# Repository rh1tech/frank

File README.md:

# FRANK

FRANK is a hardware emulation platform built around the Raspberry Pi RP2350 (Pico 2 modules and RP2350A QFN). RP2040 / Pico still works in FRANK's socket, but in practice only a handful of firmware (mainly the older ZX Spectrum cores) still targets RP2040. Everything modern (IBM PC, NES, SNES, Genesis, the DOOM / id Tech 1 ports, FRANK OS, and so on) is RP2350-only.

It started as a fork of the [Murmulator](https://murmulator.tilda.ws/) project by [Alex Ekb](https://t.me/Alex_Eburg). Over time it picked up extra video outputs, audio paths, USB and WiFi support, and several form factors.

The name comes from "Frankenstein". The board is stitched together from parts of different projects, so the name stuck.

## Looking for an older board?

This repository now ships only the boards under `hardware/` that are actively maintained. The `accessories/` and `archive/` directories are gone. Older revisions, retired boards, and accessory adapters such as HDMI2VGA and USB2PS2 live in [rh1tech/frank-archive](https://github.com/rh1tech/frank-archive).

Experimental and work-in-progress designs live in [rh1tech/frank-lab](https://github.com/rh1tech/frank-lab).

## The boards in this repo

Ten maintained boards and one published prototype, each with its own KiCad project, gerbers, BOM and assembly drawings, plus two add-on modules ([TurboSound](#modules) and [Hecate](#modules)) and three [retro-CPU boards](#retro-cpu-boards).

| Board | Render | PCB size | Compute | Best for |
|-------|:------:|----------|---------|----------|
| [FRANK Next](./hardware/frank_next) |  | 99.0 × 53.98 mm | RP2350B + RP2350A, both on-board | **Flagship.** Two RP2350 dies, on-board ESP8266EX WiFi, CH343P console, three USB-A host ports. |
| [MegaFRANK](./hardware/megafrank) |  | 149.9 × 99.5 mm | Pimoroni PGA2350 (RP2350B module) | Maximal board — every output plus on-board dual-AY TurboSound, DS3231 RTC and dual power input. |
| [FRANK PGA](./hardware/frank_pga) |  | 99.5 × 83.1 mm | Pimoroni PGA2350 (RP2350A module) | Every output on one PCB, native USB host with multiplexer, ESD-protected. |
| [FRANK](./hardware/frank) |  | 99.5 × 83.1 mm | Raspberry Pi Pico / Pico 2 (socket) + RP2040-Zero | Socketed alternative. Easiest to solder, swap Pico modules at will, USB-to-PS/2 helper on board. |
| [Old Skool FRANK](./hardware/oldskool) |  | 100.0 × 79.0 mm | Pimoroni PGA2350 (RP2350B module) | The retro-connector board: HDMI **and** VGA, hardware PS/2, DB9 gamepad. Only 2-layer design, easiest to hand-assemble. |
| [MiniFRANK](./hardware/minifrank) |  | 85.6 × 53.98 mm | RP2350A QFN, on-board | Compact full-feature board with WiFi, VGA, HDMI and one gamepad port. |
| [FRANK Core 2U](./hardware/frank_core2u) |  | 67.0 × 55.0 mm | RP2350B + RP2350A, both on-board | Smallest usable dual-die board. Video, sound, storage and USB only — no WiFi, no RTC. |
| [FRANK Core 2 Proto](./hardware/frank_core2_proto) |  | 55.0 × 55.0 mm | RP2350B + RP2350A, both on-board | Prototype. Core 2U without the USB host side — the dual-die topology at its smallest. |
| [MicroFRANK](./hardware/microfrank) |  | 32 × 74 mm | RP2350A QFN, on-board | Smallest single-die board. HDMI only, no hardware PS/2 or DB9 gamepad. Keyboards, mice and gamepads connect over the stacked USB host. |
| [ZeroFRANK](./hardware/zerofrank) |  | 65 × 25 mm | RP2350A QFN, on-board | Smallest RP2350A board. HDMI only, USB host for input, on-board flash + PSRAM + I²S audio. |
| [Nyx](./hardware/nyx) |  | 51 × 21 mm | RP2350B QFN, on-board | Open-source Pico 2 clone with built-in PSRAM. Drop-in replacement for Pico Plus 2 in the FRANK socket. |

The full-size and compact boards use the M2 GPIO layout, so any firmware build for M2 runs on them (subject to the feature differences below). FRANK Next, Core 2U and Core 2 Proto are the exception: they carry two RP2350 dies and firmware must be built for that split, or the slave simply sits idle. Nyx is a compute module — it plugs into the FRANK socket and provides the RP2350B, flash and PSRAM; the FRANK motherboard provides all the I/O.

### Comparison: full-size boards

| Feature | MegaFRANK | FRANK PGA | FRANK | Old Skool |
|---------|:---------:|:---------:|:-----:|:---------:|
| Compute | Pimoroni PGA2350 | Pimoroni PGA2350 | Pico / Pico 2 (socket) | Pimoroni PGA2350 |
| Copper layers | 4 | 4 | 4 | **2** |
| On-board flash | via module | via module | via module | via module |
| On-board PSRAM | via module | via module | via module | via module |
| HDMI output | Yes | Yes | Yes | Yes |
| VGA output | Yes | Yes | Yes | Yes |
| Composite (RCA) | Yes | Yes | Yes | — |
| TFT display header | Yes | Yes | Yes | — |
| Hardware PS/2 port | Yes | Yes | Yes | Yes |
| USB-emulated PS/2 (RP2040-Zero) | — | — | Yes | — |
| Gamepad ports (DB9) | 2 | 2 | 2 | 1 |
| Stacked USB Type-A host | Yes | Yes | Yes | Yes |
| USB hub | MW7211A | MW7211A | MW7211A | MW7211A |
| USB host multiplexer | 74HC4052D | 74HC4052D | — | 74HC4052 |
| USBLC6 ESD protection | Yes | Yes | — | — |
| WiFi | ESP-01S socket | ESP-01S socket | ESP-01S socket | ESP-01S socket |
| Real-time clock | DS3231 | — | — | — |
| Tape input (3.5mm) | Yes | Yes | Yes | Yes |
| Audio DAC | TDA1387 | TDA1387 | TDA1387 | TDA1545A + LM358 |
| PAM8403 speaker amp | Yes | Yes | Yes | — |
| Power input | DC barrel jack (×2) | DC barrel jack | DC barrel jack | USB-C / USB-B |
| Voltage regulator | MP1584 buck + AMS1117 LDO | MP1584 buck + AMS1117 LDO | MP1584 buck + AMS1117 LDO | AMS1117 LDO |
| Mounting holes | 4 × 2.7 mm | 4 × 2.7 mm | 4 × 2.7 mm | 4 × 2.7 mm |

On-board TurboSound (dual YM2149), a DS3231 real-time clock and a DS2401 silicon serial number are unique to MegaFRANK. Old Skool FRANK is the only 2-layer board in the repo, which makes it the friendliest to hand-assembly and rework.

### Comparison: compact boards

| Feature | FRANK Next | MiniFRANK | Core 2U | Core 2 Proto | MicroFRANK | ZeroFRANK |
|---------|:----------:|:---------:|:-------:|:------------:|:----------:|:---------:|
| Compute | RP2350B + RP2350A | RP2350A QFN | RP2350B + RP2350A | RP2350B + RP2350A | RP2350A QFN | RP2350A QFN |
| On-board flash | 2 × W25Q128 | W25Q128 | 2 × W25Q128 | 2 × W25Q128 | W25Q128 | W25Q128 |
| On-board PSRAM | 2 × 8 MB | 8 MB | 2 × 8 MB | 2 × 8 MB | 8 MB | 8 MB |
| HDMI output | Yes | Yes | Yes | Yes | Yes | Yes |
| VGA output | — | Yes | — | — | — | — |
| Hardware PS/2 port | — | Yes | — | — | — | — |
| Gamepad ports (DB9) | — | 1 | — | — | — | — |
| USB Type-A host ports | 3 | 2 (stacked) | 2 | — | 2 (stacked) | — (USB-C PIO host) |
| USB hub | CH334F | MW7211A | MW7211A | — | MW7211A | — |
| USB host multiplexer | TS3USB221 × 2 | TS3USB221 | TS3USB221 | — | TS3USB221 | — |
| USB serial bridge | CH343P | — | — | — | — | — |
| WiFi | ESP8266EX on-board | ESP-01S socket | — | — | — | — |
| Real-time clock | DS3231MZ | — | — | — | — | — |
| Tape input (3.5mm) | Yes | Yes | Yes | — | — | — |
| Audio DAC | TLV320DAC3100 | TDA1387 | TDA1387T + LM358 | TDA1387T + LM358 | TDA1387 | TDA1387 |
| Power input | USB-C | USB-C | USB-C | USB-C × 2 | USB-C | USB-C |
| Voltage regulator | SY8089 buck | AMS1117 LDO | AMS1117 LDO | AMS1117 LDO | ME6211 LDO | AMS1117 LDO |
| Mounting holes | 4 × 2.5 mm plated | 4 × 2.7 mm | 4 × 2.5 mm plated | 4 × 2.5 mm plated | 4 × 2.7 mm | 4 × 2.7 mm |

FRANK Next, Core 2U and Core 2 Proto share the dual-RP2350 architecture: an RP2350B master for emulation and an RP2350A slave for USB host, audio and housekeeping. Core 2U and Core 2 Proto come from a different subsystem generation than FRANK Next — ESP-PSRAM64H memory, a discrete TDA1387T audio chain instead of the TLV320DAC3100 codec, an AMS1117 LDO instead of a switching buck, and no WiFi or RTC. Core 2 Proto is Core 2U minus its host side: same two dies, no hub, no USB-A, no tape input and no power switch.

## Retro CPU boards

These are not emulation boards. Each carries a real vintage CPU in a DIP-40 socket, with an RP2350B acting as the chipset — memory, video, storage and I/O. They do not run the FRANK emulation firmware; each has its own chipset firmware.

| Board | Render | PCB size | CPU | Notes |
|-------|:------:|----------|-----|-------|
| [XT8086 Alpha](./hardware/xt8086_alpha) |  | 99.9 × 78.0 mm | Intel 8086 (minimum mode) | The earlier 8086 design: PGA2350 module, VGA and composite outputs. Superseded by XT8086 Beta, now in [frank-lab](https://github.com/rh1tech/frank-lab). |

### Modules

Two add-on modules ship alongside the boards:

| Module | Render | PCB size | What it is |
|--------|:------:|----------|------------|
| [TurboSound](./hardware/turbosound) |  | 42 × 79.5 mm | Dual YM2149 / AY-3-8910 sound expansion (socketed DIP-40). **Currently supported only by [MiniFRANK](./docs/minifrank.md)** via its expansion header. |
| [Hecate](./hardware/hecate) |  | 53 × 29 mm | Standalone RP2040 USB-to-PS/2 bridge board. Runs the [Hecate firmware](https://github.com/rh1tech/hecate); presents USB keyboards and mice as PS/2 devices. |

## Supported software

Over thirty emulators and native ports run on FRANK boards.

### Console emulators

| Firmware | Platform | Repository | PSRAM required |
|----------|----------|------------|----------------|
| frank-nes | NES / Famicom (Dendy) | [frank-nes](https://github.com/rh1tech/frank-nes) | Yes (8 MB) |
| frank-snes | SNES / Super Famicom | [frank-snes](https://github.com/rh1tech/frank-snes) | Yes (8 MB) |
| frank-genesis | Sega Genesis / Mega Drive | [frank-genesis](https://github.com/rh1tech/frank-genesis) | Yes (8 MB) |
| frank-c64 | Commodore 64 | [frank-c64](https://github.com/rh1tech/frank-c64) | Yes (8 MB) |
| frank-apple | Apple IIe | [frank-apple](https://github.com/rh1tech/frank-apple) | Optional |
| frank-msx | MSX / MSX2 / MSX2+ (fMSX core) | [frank-msx](https://github.com/rh1tech/frank-msx) | Yes (8 MB) |

### PC emulation

| Firmware | Platform | Repository | PSRAM required |
|----------|----------|------------|----------------|
| frank-386 | IBM PC i386 (DOS, Windows 3.x/95, Linux) | [frank-386](https://github.com/rh1tech/frank-386) | Yes (8 MB) |

### Game engine ports

| Firmware | Game | Repository | PSRAM required |
|----------|------|------------|----------------|
| frank-idtech1 | DOOM, Heretic, Hexen, Strife (all-in-one) | [frank-idtech1](https://github.com/rh1tech/frank-idtech1) | Yes (8 MB) |
| frank-doom | DOOM (standalone) | [frank-doom](https://github.com/rh1tech/frank-doom) | Yes (8 MB) |
| frank-heretic | Heretic | [frank-heretic](https://github.com/rh1tech/frank-heretic) | Yes (8 MB) |
| frank-wolf3d | Wolfenstein 3D | [frank-wolf3d](https://github.com/rh1tech/frank-wolf3d) | Yes (8 MB) |
| frank-duke3d | Duke Nukem 3D | [frank-duke3d](https://github.com/rh1tech/frank-duke3d) | Yes (8 MB) |
| frank-prince | Prince of Persia | [frank-prince](https://github.com/rh1tech/frank-prince) | Yes (8 MB) |
| frank-digger | Digger Remastered | [frank-digger](https://github.com/rh1tech/frank-digger) | No |
| frank-quest | ScummVM (AGI, SCI, SCUMM v1–v7, GOB, KYRA — King's Quest, Monkey Island, Day of the Tentacle, Full Throttle, Gobliiins, Kyrandia and more) | [frank-quest](https://github.com/rh1tech/frank-quest) | Yes (8 MB) |

### OS and utilities

| Firmware | Description | Repository | PSRAM required |
|----------|-------------|------------|----------------|
| frank-os | Full desktop OS (Windows 95-style GUI, apps, built-in emulators) | [frank-os](https://github.com/rh1tech/frank-os) | Yes (8 MB) |
| frank-kickstart | UF2 firmware launcher with SD card browser | [frank-kickstart](https://github.com/rh1tech/frank-kickstart) | Optional |
| frank-manul | Text-mode web browser (HTTP/HTTPS via ESP-01 WiFi) | [frank-manul](https://github.com/rh1tech/frank-manul) | Yes (8 MB) |
| frank-netcard | AT modem firmware for the ESP-01 WiFi module | [frank-netcard](https://github.com/rh1tech/frank-netcard) | No |

### Murmulator firmware

The original [Murmulator](https://murmulator.ru/) project provides additional firmware that runs on FRANK boards as well:

**ZX Spectrum cores:** ZX Spectrum 48K / 128K / +3e (tecnocat, pico-spec, frut-bat, ZX Speccy P, murmulator), ZX Elf (pico-alf).

**Other cross-platform emulators:** MS-DOS IBM PC XT 8088, BK-0010 / BK-0011M, Radio 86RK, Macintosh, Atari 800, NES / Famicom / Dendy, Sega Master System / Game Gear, NEC PC Engine / TurboGrafx-16, Nintendo GameBoy / GameBoy Color, Watara Supervision, Atari Lynx, Bandai Wonderswan / Wonderswan Color, NeoGeo Pocket Color, Gamate, Game & Watch / Elektronika.

**Tools and applications:** MurmulatorOS, Picomite MMBasic, VersaTerm, the original Murmulator bootloader.

### Other compatible boards

Most firmware also runs on:

- Murmulator (M1 and M2)
- Olimex PICO-PC (some firmware)
- Waveshare RP2350-PiZero (some firmware)

## Getting started

1. Order or fab the PCB (gerbers are in each board's `gerbers/` directory).
2. Source the components using the BOM (`hardware/<board>/docs/<rev>/bom.html`).
3. Solder following the [board-specific guide](./docs/), starting with the smallest passives and working outwards.
4. Flash firmware: hold BOOTSEL on the RP chip, plug USB, release, copy a `.uf2` file to the drive that appears (or use `picotool load`).
5. Insert an SD card with ROMs, WADs or disk images.
6. Plug in a display (HDMI or VGA), keyboard (PS/2 or USB) and gamepad.

For quick switching between firmware, flash [frank-kickstart](https://github.com/rh1tech/frank-kickstart) first. It gives you a graphical launcher that re-flashes from SD without touching BOOTSEL again.

## PSRAM

Most modern firmware (frank-os, frank-quest, frank-386, frank-genesis, frank-snes, frank-msx, frank-idtech1, frank-doom and so on) needs 8 MB of PSRAM. Some firmware refuses to boot without it: frank-quest installs a custom dlmalloc backed entirely by external PSRAM (`drivers/psram_init.c`, `drivers/dlmalloc.c`), because the runtime (heap-allocated game state, decoded resources, mixer ring buffers, font caches) does not fit in the RP2350's 520 KB of SRAM.

How you get PSRAM depends on the board:

- **FRANK Next, Core 2U and Core 2 Proto**: 8 MB PSRAM per die, both dies on-board. Nothing to do.
- **MiniFRANK, MicroFRANK and ZeroFRANK**: PSRAM is already on-board (8 MB). Nothing to do.
- **FRANK PGA, MegaFRANK and Old Skool FRANK**: the Pimoroni PGA2350 module already includes 8 MB PSRAM. Nothing to do.
- **FRANK**: the socketed Pico 2 has no PSRAM by default. Three ways to fix this:
  1. **Pimoroni Pico Plus 2 (recommended).** A ready-made Pico 2 with 8 MB PSRAM. Drop it into the socket and you are done.
  2. **Build a [Nyx](./hardware/nyx)**, an open-source RP2350B board with integrated 16 MB flash and 8 MB PSRAM. Same form factor as Pico 2, drops straight into the socket.
  3. **Solder a PSRAM chip on top of the flash chip of an RP2350 clone.** SOP-8 flash chips are mostly only on clones (typically the black boards), not on a genuine Pico 2.

## Repo layout

```
hardware/      Board KiCad projects (frank_next, megafrank, frank_pga, frank,
               oldskool, minifrank, frank_core2u, frank_core2_proto, microfrank,
               zerofrank, nyx), the retro-CPU board xt8086_alpha, plus the turbosound and hecate modules
docs/          Shared component datasheets and assembly notes
software/      Pre-built UF2s. Currently ships Hecate, the USB-to-PS/2 bridge
               firmware for FRANK's on-board RP2040-Zero. Once flashed, a USB
               keyboard or mouse appears on the hardware PS/2 lines.
               Source: https://github.com/rh1tech/hecate
```

## Documentation

Each board and module has its own assembly and usage guide:

- [FRANK Next assembly and usage guide](./docs/frank_next.md)
- [MegaFRANK assembly and usage guide](./docs/megafrank.md)
- [FRANK PGA assembly and usage guide](./docs/frank_pga.md)
- [FRANK assembly and usage guide](./docs/frank.md)
- [Old Skool FRANK assembly and usage guide](./docs/oldskool.md)
- [MiniFRANK assembly and usage guide](./docs/minifrank.md)
- [FRANK Core 2U assembly and usage guide](./docs/frank_core2u.md)
- [FRANK Core 2 Proto assembly and usage guide](./docs/frank_core2_proto.md)
- [MicroFRANK assembly and usage guide](./docs/microfrank.md)
- [ZeroFRANK assembly and usage guide](./docs/zerofrank.md)
- [Nyx assembly and usage guide](./docs/nyx.md)
- [TurboSound module guide](./docs/turbosound.md)
- [Hecate (USB-to-PS/2 bridge) guide](./docs/hecate.md)

The `hardware/<board>/docs/` directories also contain auto-generated BOMs (`bom.html`) and assembly drawings (`assembly.pdf`, `schematics.pdf`) for each PCB revision.

## Links

- [rh1.tech/projects/frank](https://rh1.tech/projects/frank) — project website
- [rh1tech/frank-archive](https://github.com/rh1tech/frank-archive) — older boards and accessories
- [rh1tech/frank-lab](https://github.com/rh1tech/frank-lab) — experimental designs

### Firmware repositories

Console emulators:

- [frank-nes](https://github.com/rh1tech/frank-nes) — NES / Famicom (Dendy)
- [frank-snes](https://github.com/rh1tech/frank-snes) — SNES / Super Famicom
- [frank-genesis](https://github.com/rh1tech/frank-genesis) — Sega Genesis / Mega Drive
- [frank-c64](https://github.com/rh1tech/frank-c64) — Commodore 64
- [frank-apple](https://github.com/rh1tech/frank-apple) — Apple IIe
- [frank-msx](https://github.com/rh1tech/frank-msx) — MSX / MSX2 / MSX2+

PC emulation:

- [frank-386](https://github.com/rh1tech/frank-386) — IBM PC i386 (DOS, Windows 3.x/95, Linux)

Game engine ports:

- [frank-idtech1](https://github.com/rh1tech/frank-idtech1) — DOOM, Heretic, Hexen, Strife (all-in-one)
- [frank-doom](https://github.com/rh1tech/frank-doom) — DOOM (standalone)
- [frank-heretic](https://github.com/rh1tech/frank-heretic) — Heretic
- [frank-wolf3d](https://github.com/rh1tech/frank-wolf3d) — Wolfenstein 3D
- [frank-duke3d](https://github.com/rh1tech/frank-duke3d) — Duke Nukem 3D
- [frank-prince](https://github.com/rh1tech/frank-prince) — Prince of Persia
- [frank-digger](https://github.com/rh1tech/frank-digger) — Digger Remastered
- [frank-quest](https://github.com/rh1tech/frank-quest) — ScummVM (AGI, SCI, SCUMM, GOB, KYRA)

OS and utilities:

- [frank-os](https://github.com/rh1tech/frank-os) — Full desktop OS with built-in emulators
- [frank-kickstart](https://github.com/rh1tech/frank-kickstart) — UF2 firmware launcher
- [frank-manul](https://github.com/rh1tech/frank-manul) — Text-mode web browser
- [frank-netcard](https://github.com/rh1tech/frank-netcard) — AT modem firmware for ESP-01
- [hecate](https://github.com/rh1tech/hecate) — USB-to-PS/2 bridge for the RP2040-Zero

## Author

Mikhail Matveev — software engineer and hardware developer based in Thessaloniki, Greece. Background in software architecture, QA and open-source development. Builds retro computing hardware and writes firmware for fun. More projects at [rh1.tech](https://rh1.tech).

## License

&copy; 2026 Mikhail Matveev, <xtreme@rh1.tech>

GPL v3. See [LICENSE](./LICENSE).

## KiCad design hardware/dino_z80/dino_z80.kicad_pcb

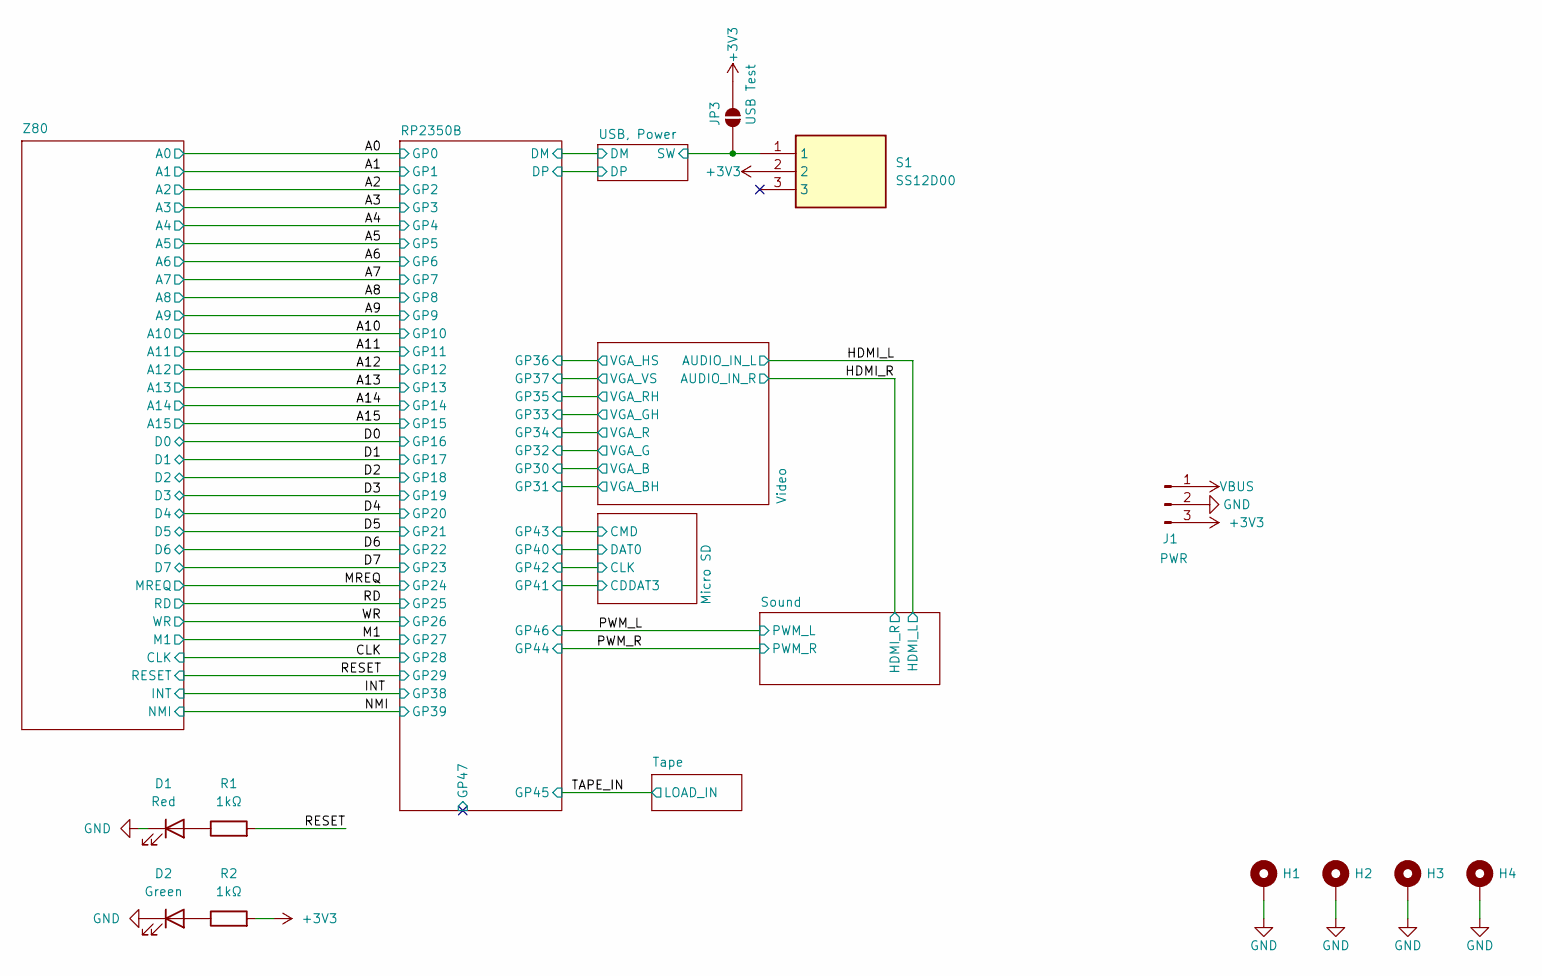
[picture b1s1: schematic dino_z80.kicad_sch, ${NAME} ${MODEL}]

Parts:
D1: Red; LED_0805_2012Metric_Pad1.15x1.40mm_HandSolder
D2: Green; LED_0805_2012Metric_Pad1.15x1.40mm_HandSolder
H1, H2, H3, H4: Hole 2.5mm; MountingHole_2.5mm_Pad_Via
J1: PWR; PinHeader_1x03_P2.54mm_Vertical
JP3: USB Test; SolderJumper-2_P1.3mm_Open_Pad1.0x1.5mm
R1, R2: 1kΩ; R_0603_1608Metric
S1: SS12D00; Switch_Slide_SS12D00; Mouser Part Number 611-SK12D07VG3NS

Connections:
+3V3: J1.3, JP3.1 (A), R2.2, S1.2; also elsewhere on the board
/RESET: R1.2; also elsewhere on the board
/USB, Power/SW: JP3.2 (B), S1.1; also elsewhere on the board
GND: D1.1 (K), D2.1 (K), H1.1 (1_1), H2.1 (1_1), H3.1 (1_1), H4.1 (1_1), J1.2; also elsewhere on the board
unnamed: D1.2 (A), R1.1
unnamed: D2.2 (A), R2.1
VBUS: J1.1; also elsewhere on the board

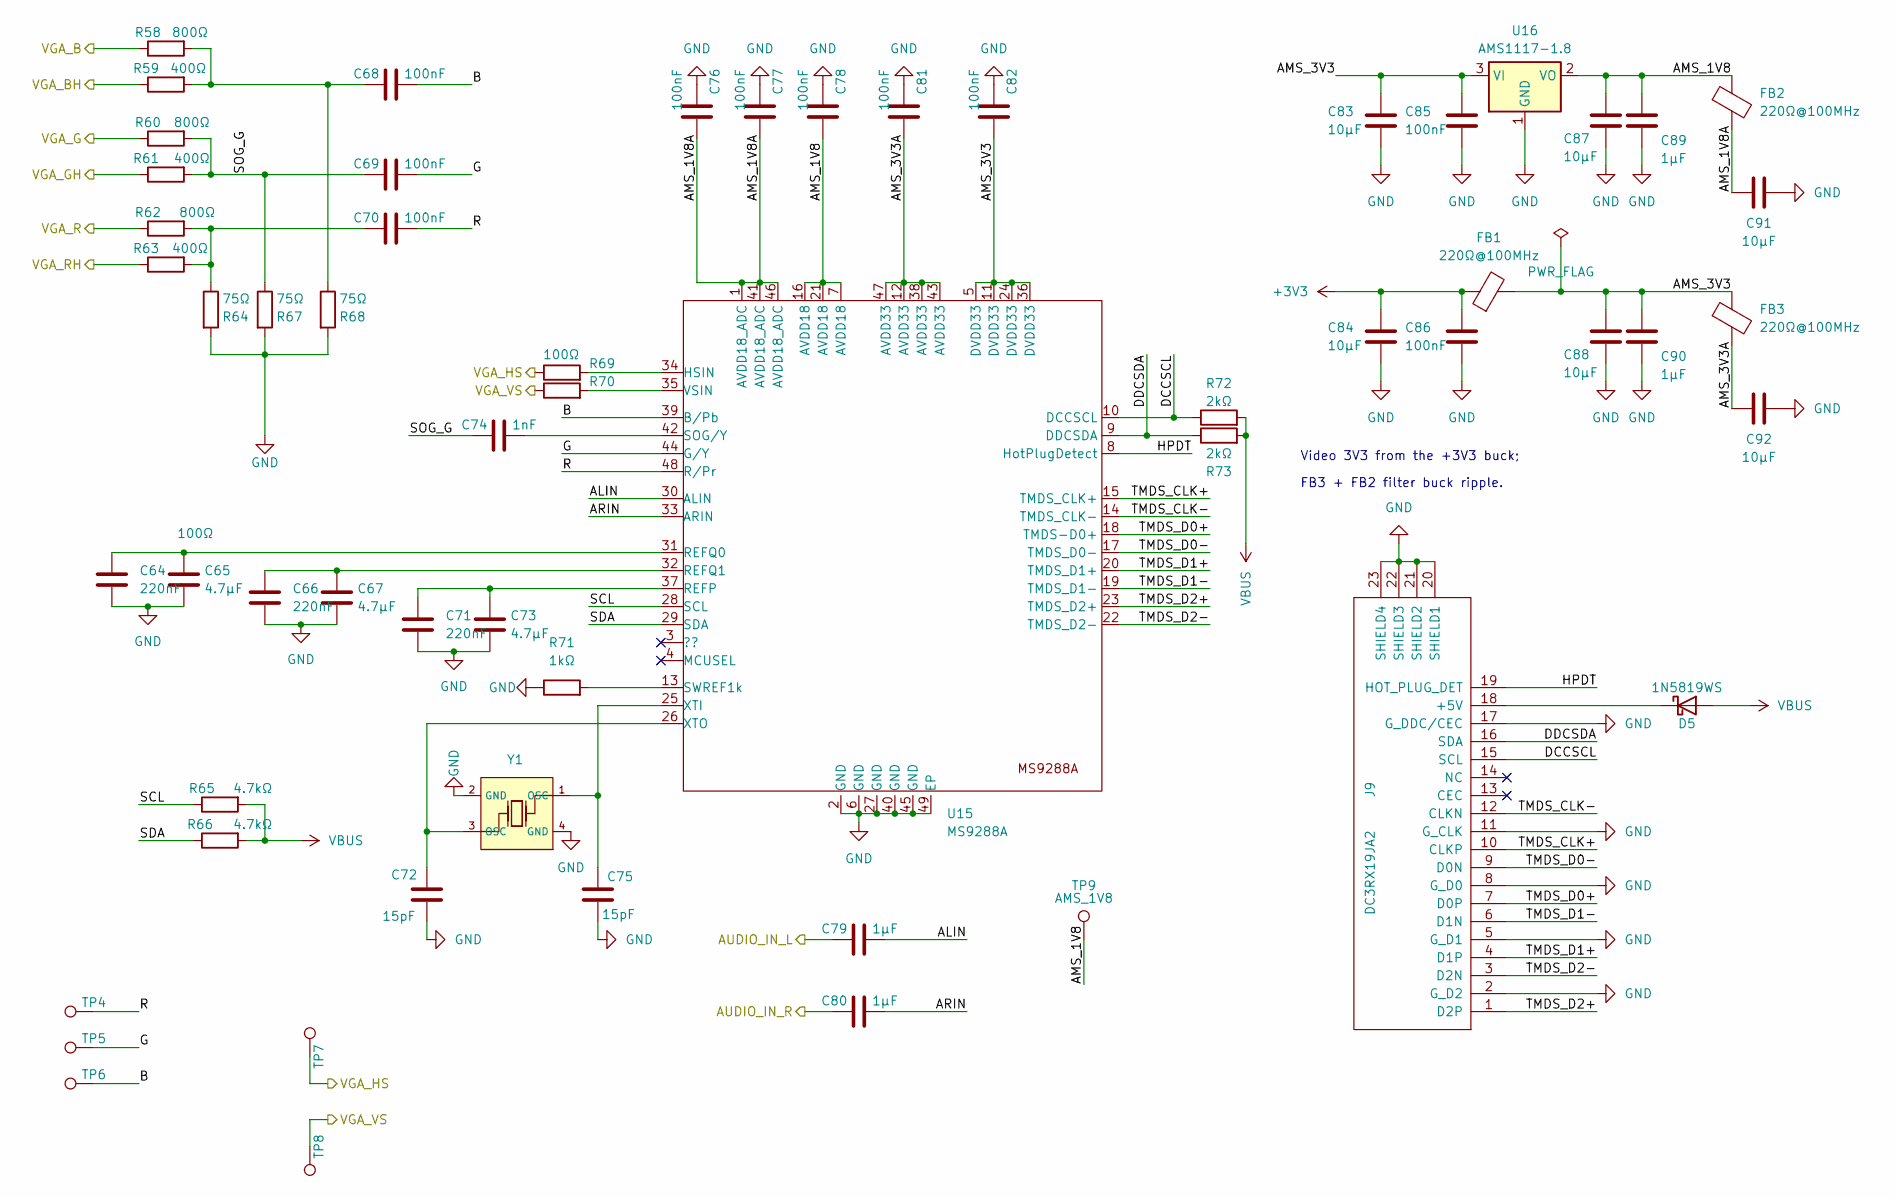
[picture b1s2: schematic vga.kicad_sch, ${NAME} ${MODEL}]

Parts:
C64, C66, C71: 220nF; C_0603_1608Metric
C65, C67, C73: 4.7µF; C_0603_1608Metric
C68, C69, C70, C76, C77, C78, C81, C82, C85, C86: 100nF; C_0603_1608Metric
C72, C75: 15pF; C_0603_1608Metric
C74: 1nF; C_0603_1608Metric
C79, C80, C89, C90: 1µF; C_0603_1608Metric
C83, C84, C87, C88, C91, C92: 10µF; C_0603_1608Metric
D5: 1N5819WS; D_SOD-323
FB1, FB2, FB3: 220Ω@100MHz; L_0805_2012Metric
J9: DC3RX19JA2; HDMI_Female
R58, R60, R62: 800Ω; R_0603_1608Metric
R59, R61, R63: 400Ω; R_0603_1608Metric
R64, R67, R68: 75Ω; R_0603_1608Metric
R65, R66: 4.7kΩ; R_0603_1608Metric
R69, R70: 100Ω; R_0603_1608Metric
R71: 1kΩ; R_0603_1608Metric
R72, R73: 2kΩ; R_0603_1608Metric
TP4: R; TestPoint_Pad_1.0x1.0mm
TP5: G; TestPoint_Pad_1.0x1.0mm
TP6: B; TestPoint_Pad_1.0x1.0mm
TP7: HS; TestPoint_Pad_1.0x1.0mm
TP8: VS; TestPoint_Pad_1.0x1.0mm
TP9: AMS_1V8; TestPoint_Pad_1.0x1.0mm
U15: MS9288A; QFN-48_6x6mm_P0.4mm
U16: AMS1117-1.8; SOT-223-3_TabPin2
Y1: 24.576MHz; Crystal_SMD_2520-4Pin

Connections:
+3V3: C84.1, C86.1, FB1.1; also elsewhere on the board
/HDMI_L: C79.2; also elsewhere on the board
/HDMI_R: C80.2; also elsewhere on the board
/RP2350B/GP30: R58.1; also elsewhere on the board
/RP2350B/GP31: R59.1; also elsewhere on the board
/RP2350B/GP32: R60.1; also elsewhere on the board
/RP2350B/GP33: R61.1; also elsewhere on the board
/RP2350B/GP34: R62.1; also elsewhere on the board
/RP2350B/GP35: R63.1; also elsewhere on the board
/RP2350B/GP36: R69.1, TP7.1 (1_1); also elsewhere on the board
/RP2350B/GP37: R70.1, TP8.1 (1_1); also elsewhere on the board
/Video/ALIN: C79.1, U15.30 (ALIN)
/Video/AMS_1V8: C78.1, C87.1, C89.1, FB2.1, TP9.1 (1_1), U15.7 (AVDD18), U15.16 (AVDD18), U15.21 (AVDD18), U16.2 (VO)
/Video/AMS_1V8A: C76.1, C77.1, C91.1, FB2.2, U15.1 (AVDD18_ADC), U15.41 (AVDD18_ADC), U15.46 (AVDD18_ADC)
/Video/AMS_3V3: C82.1, C83.1, C85.1, C88.1, C90.1, FB1.2, FB3.1, U15.5 (DVDD33), U15.11 (DVDD33), U15.24 (DVDD33), U15.36 (DVDD33), U16.3 (VI)
/Video/AMS_3V3A: C81.1, C92.1, FB3.2, U15.12 (AVDD33), U15.38 (AVDD33), U15.43 (AVDD33), U15.47 (AVDD33)
/Video/ARIN: C80.1, U15.33 (ARIN)
/Video/B: C68.1, TP6.1 (1_1), U15.39 (B/Pb)
/Video/DCCSCL: J9.15 (SCL), R72.1, U15.10 (DCCSCL)
/Video/DDCSDA: J9.16 (SDA), R73.1, U15.9 (DDCSDA)
/Video/G: C69.1, TP5.1 (1_1), U15.44 (G/Y)
/Video/HPDT: J9.19 (HOT_PLUG_DET), U15.8 (HotPlugDetect)
/Video/R: C70.1, TP4.1 (1_1), U15.48 (R/Pr)
/Video/SCL: R65.1, U15.28 (SCL)
/Video/SDA: R66.1, U15.29 (SDA)
/Video/SOG_G: C69.2, C74.2, R60.2, R61.2, R67.1
/Video/TMDS_CLK+: J9.10 (CLKP), U15.15 (TMDS_CLK+)
/Video/TMDS_CLK-: J9.12 (CLKN), U15.14 (TMDS_CLK-)
/Video/TMDS_D0+: J9.7 (D0P), U15.18 (TMDS-D0+)
/Video/TMDS_D0-: J9.9 (D0N), U15.17 (TMDS_D0-)
/Video/TMDS_D1+: J9.4 (D1P), U15.20 (TMDS_D1+)
/Video/TMDS_D1-: J9.6 (D1N), U15.19 (TMDS_D1-)
/Video/TMDS_D2+: J9.1 (D2P), U15.23 (TMDS_D2+)
/Video/TMDS_D2-: J9.3 (D2N), U15.22 (TMDS_D2-)
GND: C64.2, C65.2, C66.2, C67.2, C71.2, C72.2, C73.2, C75.2, C76.2, C77.2, C78.2, C81.2, C82.2, C83.2, C84.2, C85.2, C86.2, C87.2, C88.2, C89.2, C90.2, C91.2, C92.2, J9.2 (G_D2), J9.5 (G_D1), J9.8 (G_D0), J9.11 (G_CLK), J9.17 (G_DDC/CEC), J9.20 (SHIELD1), J9.21 (SHIELD2), J9.22 (SHIELD3), J9.23 (SHIELD4), R64.2, R67.2, R68.2, R71.1, U15.2 (GND), U15.6 (GND), U15.27 (GND), U15.40 (GND), U15.45 (GND), U15.49 (EP), U16.1 (GND), Y1.2 (GND), Y1.4 (GND); also elsewhere on the board
unnamed: C68.2, R58.2, R59.2, R68.1
unnamed: C70.2, R62.2, R63.2, R64.1
unnamed: D5.1 (K), J9.18 (+5V)
unnamed: R69.2, U15.34 (HSIN)
unnamed: C71.1, C73.1, U15.37 (REFP)
unnamed: C64.1, C65.1, U15.31 (REFQ0)
unnamed: C66.1, C67.1, U15.32 (REFQ1)
unnamed: C74.1, U15.42 (SOG/Y)
unnamed: R71.2, U15.13 (SWREF1k)
unnamed: R70.2, U15.35 (VSIN)
unnamed: C75.1, U15.25 (XTI), Y1.1 (OSC)
unnamed: C72.1, U15.26 (XTO), Y1.3 (OSC)
VBUS: D5.2 (A), R65.2, R66.2, R72.2, R73.2; also elsewhere on the board

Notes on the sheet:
FB3 + FB2 filter buck ripple.
Video 3V3 from the +3V3 buck;

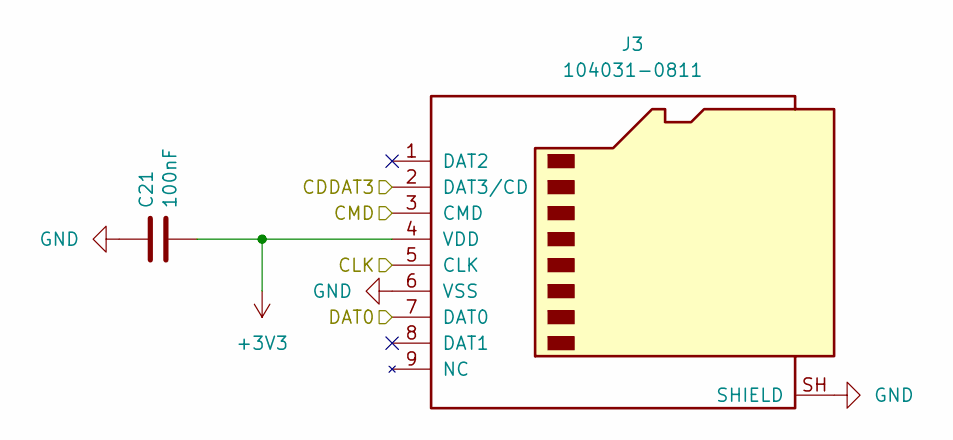
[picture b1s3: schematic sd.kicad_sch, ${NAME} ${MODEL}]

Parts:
C21: 100nF; C_0603_1608Metric
J3: 104031-0811; MicroSD_SMD_Long

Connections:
+3V3: C21.2, J3.4 (VDD); also elsewhere on the board
/Micro SD/CDDAT3: J3.2 (DAT3/CD); also elsewhere on the board
/Micro SD/CLK: J3.5 (CLK); also elsewhere on the board
/Micro SD/CMD: J3.3 (CMD); also elsewhere on the board
/Micro SD/DAT0: J3.7 (DAT0); also elsewhere on the board
GND: C21.1, J3.6 (VSS), J3.SH (SHIELD); also elsewhere on the board

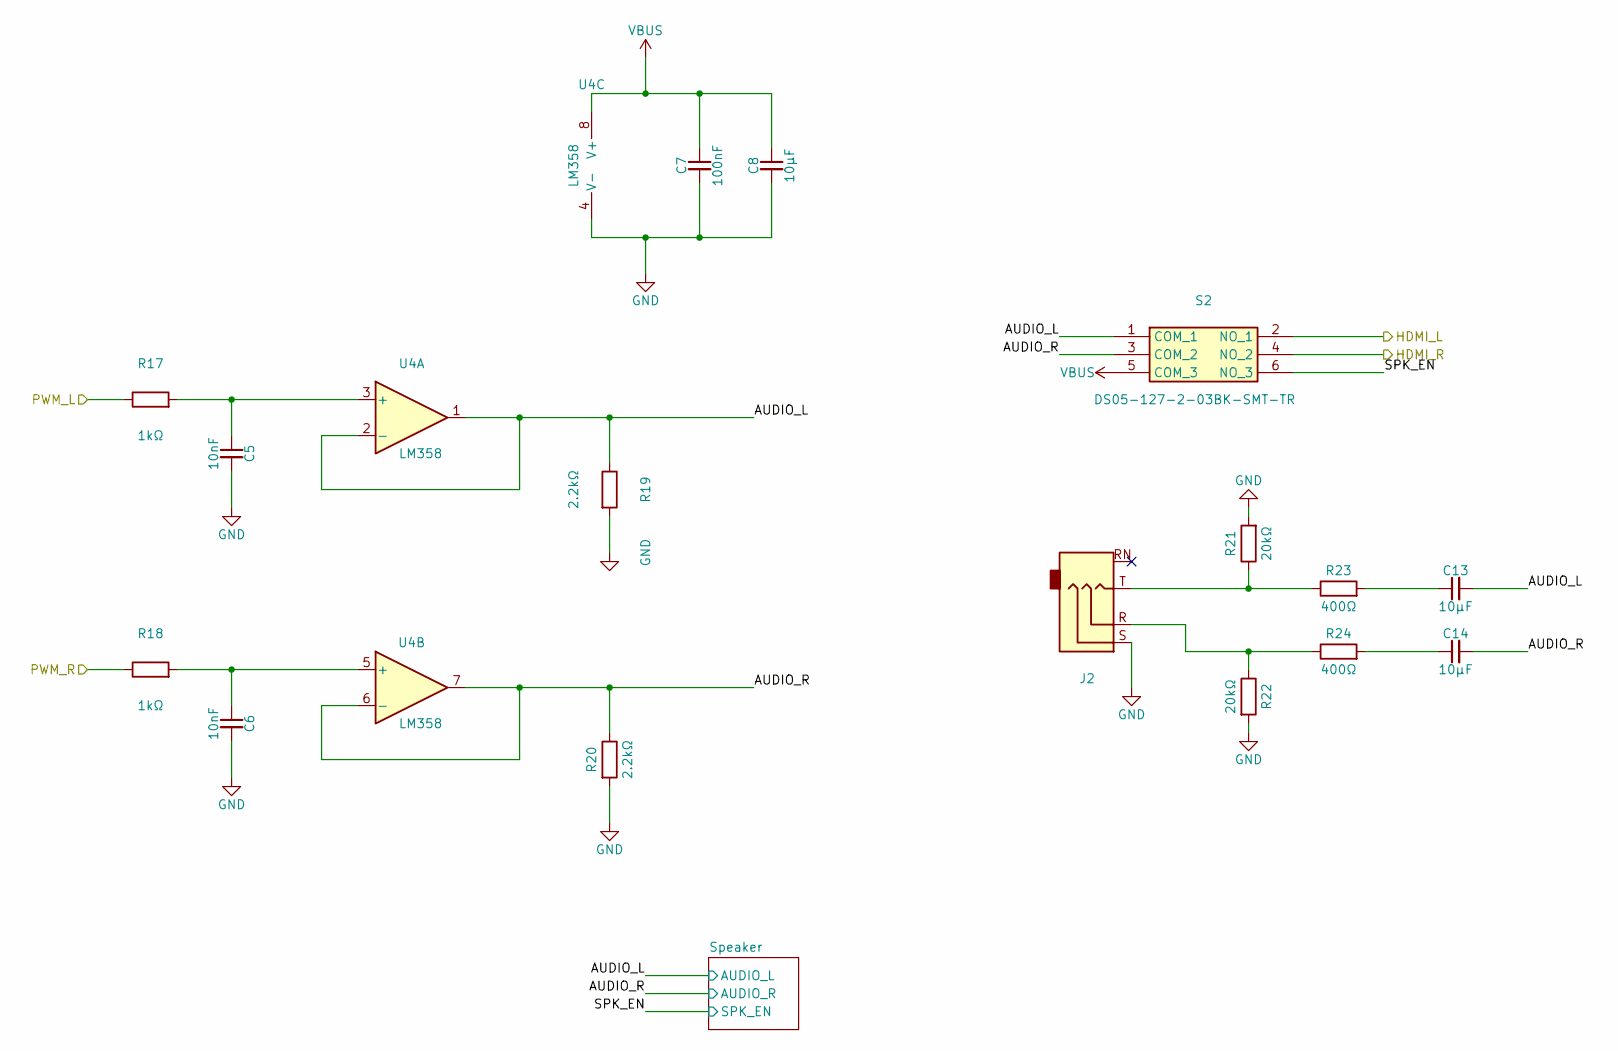
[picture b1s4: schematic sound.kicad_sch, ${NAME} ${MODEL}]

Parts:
C5, C6: 10nF; C_0603_1608Metric
C7: 100nF; C_0603_1608Metric
C8, C13, C14: 10µF; C_0603_1608Metric
J2: PJ-320D; AudioJack_3.5mm_PJ320D_AudioOut
R17, R18: 1kΩ; R_0603_1608Metric
R19, R20: 2.2kΩ; R_0603_1608Metric
R21, R22: 20kΩ; R_0603_1608Metric
R23, R24: 400Ω; R_0603_1608Metric
S2: DS05-127-2-03BK-SMT-TR; SW_DIP_DS05-127-2-03BK-SMT
U4: LM358; SOIC-8_3.9x4.9mm_P1.27mm

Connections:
/HDMI_L: S2.2 (NO_1); also elsewhere on the board
/HDMI_R: S2.4 (NO_2); also elsewhere on the board
/PWM_L: R17.1; also elsewhere on the board
/PWM_R: R18.1; also elsewhere on the board
/Sound/AUDIO_L: C13.2, R19.1, S2.1 (COM_1), U4.1, U4.2 (-); also elsewhere on the board
/Sound/AUDIO_R: C14.2, R20.1, S2.3 (COM_2), U4.6 (-), U4.7; also elsewhere on the board
/Sound/SPK_EN: S2.6 (NO_3); also elsewhere on the board
GND: C5.2, C6.2, C7.2, C8.2, J2.S, R19.2, R20.2, R21.2, R22.2, U4.4 (V-); also elsewhere on the board
unnamed: C13.1, R23.2
unnamed: C14.1, R24.2
unnamed: J2.R, R22.1, R24.1
unnamed: J2.T, R21.1, R23.1
unnamed: C5.1, R17.2, U4.3 (+)
unnamed: C6.1, R18.2, U4.5 (+)
VBUS: C7.1, C8.1, S2.5 (COM_3), U4.8 (V+); also elsewhere on the board

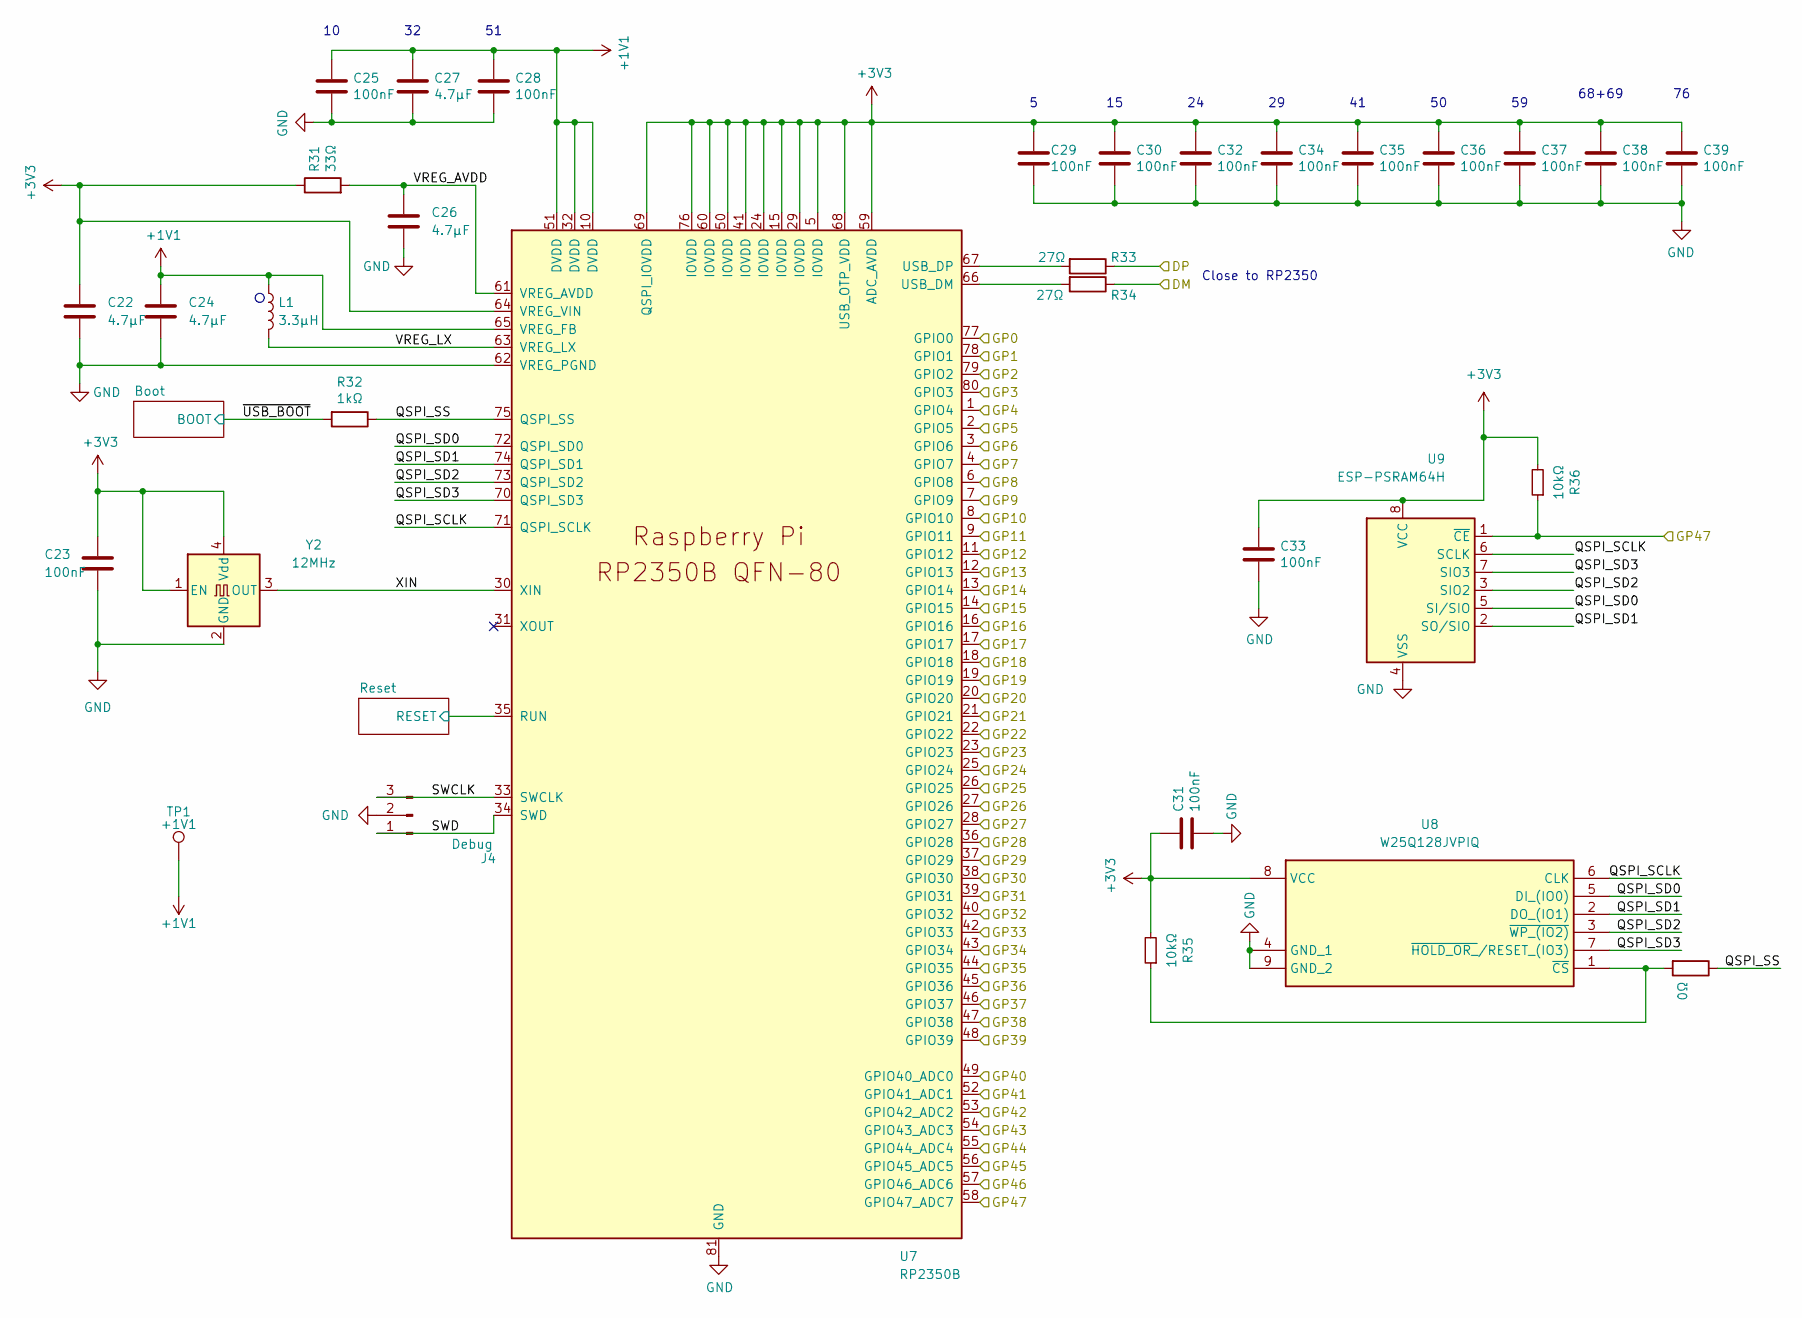
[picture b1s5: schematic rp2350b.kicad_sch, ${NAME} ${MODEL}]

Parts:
C22, C24, C26, C27: 4.7µF; C_0603_1608Metric
C23, C25, C28, C29, C30, C31, C32, C33, C34, C35, C36, C37, C38, C39: 100nF; C_0603_1608Metric
J4: Debug; JST_SH_1x03_P1.00mm_Vertical
L1: 3.3µH; L_LQH2MCN100K02L
R31: 33Ω; R_0603_1608Metric
R32: 1kΩ; R_0603_1608Metric
R33, R34: 27Ω; R_0603_1608Metric
R35, R36: 10kΩ; R_0603_1608Metric
R37: 0Ω; R_0603_1608Metric
TP1: +1V1; TestPoint_Pad_1.0x1.0mm
U7: RP2350B; RP2350-QFN-80_10x10_P0.4mm
U8: W25Q128JVPIQ; SON127P600X500X80-9N-D; Mouser Part Number 454-W25Q128JVPIQ
U9: ESP-PSRAM64H; SO-8
Y2: 12MHz; Oscillator_SMD_3225_4Pin

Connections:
+1V1: C24.1, C25.1, C27.1, C28.1, L1.1, TP1.1 (1_1), U7.10 (DVDD), U7.32 (DVDD), U7.51 (DVDD), U7.65 (VREG_FB)
+3V3: C22.1, C23.1, C29.1, C30.1, C31.1, C32.1, C33.1, C34.1, C35.1, C36.1, C37.1, C38.1, C39.1, R31.1, R35.2, R36.2, U7.5 (IOVDD), U7.15 (IOVDD), U7.24 (IOVDD), U7.29 (IOVDD), U7.41 (IOVDD), U7.50 (IOVDD), U7.59 (ADC_AVDD), U7.60 (IOVDD), U7.64 (VREG_VIN), U7.68 (USB_OTP_VDD), U7.69 (QSPI_IOVDD), U7.76 (IOVDD), U8.8 (VCC), U9.8 (VCC), Y2.1 (EN), Y2.4 (Vdd); also elsewhere on the board
/A0: U7.77 (GPIO0); also elsewhere on the board
/A1: U7.78 (GPIO1); also elsewhere on the board
/A2: U7.79 (GPIO2); also elsewhere on the board
/A3: U7.80 (GPIO3); also elsewhere on the board
/A4: U7.1 (GPIO4); also elsewhere on the board
/A5: U7.2 (GPIO5); also elsewhere on the board
/A6: U7.3 (GPIO6); also elsewhere on the board
/A7: U7.4 (GPIO7); also elsewhere on the board
/A8: U7.6 (GPIO8); also elsewhere on the board
/A9: U7.7 (GPIO9); also elsewhere on the board
/A10: U7.8 (GPIO10); also elsewhere on the board
/A11: U7.9 (GPIO11); also elsewhere on the board
/A12: U7.11 (GPIO12); also elsewhere on the board
/A13: U7.12 (GPIO13); also elsewhere on the board
/A14: U7.13 (GPIO14); also elsewhere on the board
/A15: U7.14 (GPIO15); also elsewhere on the board
/CLK: U7.36 (GPIO28); also elsewhere on the board
/D0: U7.16 (GPIO16); also elsewhere on the board
/D1: U7.17 (GPIO17); also elsewhere on the board
/D2: U7.18 (GPIO18); also elsewhere on the board
/D3: U7.19 (GPIO19); also elsewhere on the board
/D4: U7.20 (GPIO20); also elsewhere on the board
/D5: U7.21 (GPIO21); also elsewhere on the board
/D6: U7.22 (GPIO22); also elsewhere on the board
/D7: U7.23 (GPIO23); also elsewhere on the board
/INT: U7.47 (GPIO38); also elsewhere on the board
/M1: U7.28 (GPIO27); also elsewhere on the board
/MREQ: U7.25 (GPIO24); also elsewhere on the board
/Micro SD/CDDAT3: U7.52 (GPIO41_ADC1); also elsewhere on the board
/Micro SD/CLK: U7.53 (GPIO42_ADC2); also elsewhere on the board
/Micro SD/CMD: U7.54 (GPIO43_ADC3); also elsewhere on the board
/Micro SD/DAT0: U7.49 (GPIO40_ADC0); also elsewhere on the board
/NMI: U7.48 (GPIO39); also elsewhere on the board
/PWM_L: U7.57 (GPIO46_ADC6); also elsewhere on the board
/PWM_R: U7.55 (GPIO44_ADC4); also elsewhere on the board
/RD: U7.26 (GPIO25); also elsewhere on the board
/RESET: U7.37 (GPIO29); also elsewhere on the board
/RP2350B/DM: R34.1; also elsewhere on the board
/RP2350B/DP: R33.1; also elsewhere on the board
/RP2350B/GP30: U7.38 (GPIO30); also elsewhere on the board
/RP2350B/GP31: U7.39 (GPIO31); also elsewhere on the board
/RP2350B/GP32: U7.40 (GPIO32); also elsewhere on the board
/RP2350B/GP33: U7.42 (GPIO33); also elsewhere on the board
/RP2350B/GP34: U7.43 (GPIO34); also elsewhere on the board
/RP2350B/GP35: U7.44 (GPIO35); also elsewhere on the board
/RP2350B/GP36: U7.45 (GPIO36); also elsewhere on the board
/RP2350B/GP37: U7.46 (GPIO37); also elsewhere on the board
/RP2350B/GP47: R36.1, U7.58 (GPIO47_ADC7), U9.1 (~CE)
/RP2350B/QSPI_SCLK: U7.71 (QSPI_SCLK), U8.6 (CLK), U9.6 (SCLK)
/RP2350B/QSPI_SD0: U7.72 (QSPI_SD0), U8.5 (DI_(IO0)), U9.5 (SI/SIO)
/RP2350B/QSPI_SD1: U7.74 (QSPI_SD1), U8.2 (DO_(IO1)), U9.2 (SO/SIO)
/RP2350B/QSPI_SD2: U7.73 (QSPI_SD2), U8.3 (~WP_(IO2)), U9.3 (SIO2)
/RP2350B/QSPI_SD3: U7.70 (QSPI_SD3), U8.7 (~HOLD_OR_/RESET_(IO3)), U9.7 (SIO3)
/RP2350B/QSPI_SS: R32.1, R37.1, U7.75 (QSPI_SS)
/RP2350B/Reset/RESET: U7.35 (RUN); also elsewhere on the board
/RP2350B/SWCLK: J4.3, U7.33 (SWCLK)
/RP2350B/SWD: J4.1, U7.34 (SWD)
/RP2350B/VREG_AVDD: C26.1, R31.2, U7.61 (VREG_AVDD)
/RP2350B/VREG_LX: L1.2, U7.63 (VREG_LX)
/RP2350B/XIN: U7.30 (XIN), Y2.3 (OUT)
/RP2350B/~USB_BOOT: R32.2; also elsewhere on the board
/TAPE_IN: U7.56 (GPIO45_ADC5); also elsewhere on the board
/WR: U7.27 (GPIO26); also elsewhere on the board
GND: C22.2, C23.2, C24.2, C25.2, C26.2, C27.2, C28.2, C29.2, C30.2, C31.2, C32.2, C33.2, C34.2, C35.2, C36.2, C37.2, C38.2, C39.2, J4.2, U7.62 (VREG_PGND), U7.81 (GND), U8.4 (GND_1), U8.9 (GND_2), U9.4 (VSS), Y2.2 (GND); also elsewhere on the board
unnamed: R34.2, U7.66 (USB_DM)
unnamed: R33.2, U7.67 (USB_DP)
unnamed: R35.1, R37.2, U8.1 (~CS)

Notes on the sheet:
Close to RP2350
68+69

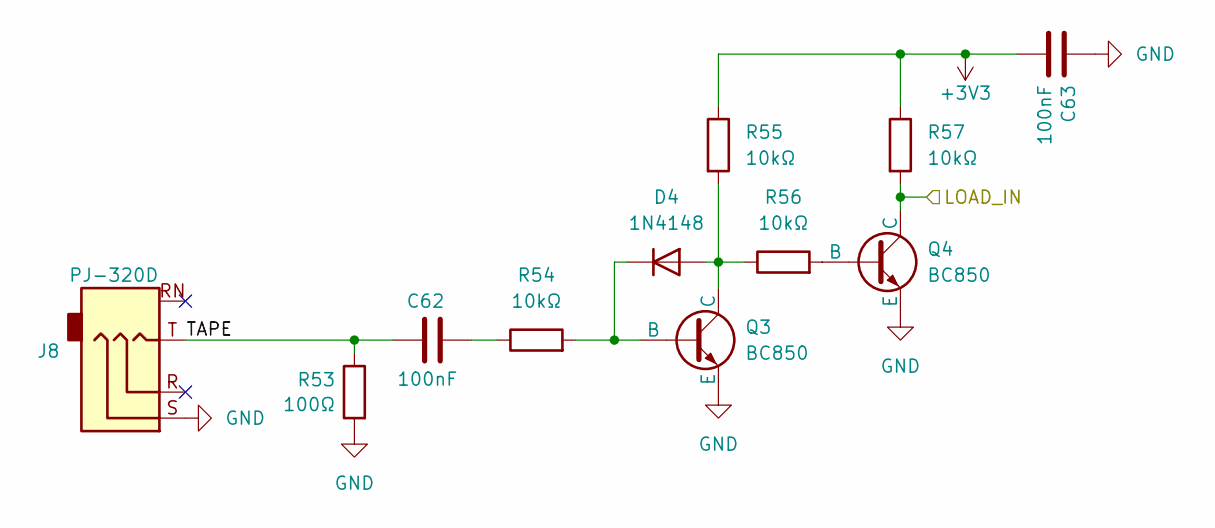
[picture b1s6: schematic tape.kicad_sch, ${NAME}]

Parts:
C62, C63: 100nF; C_0603_1608Metric; LCSC C14663
D4: 1N4148; D_SOD-323; LCSC C2128
J8: PJ-320D; AudioJack_3.5mm_PJ320D_TapeIn; LCSC C431535
Q3, Q4: BC850; SOT-23; LCSC C503377
R53: 100Ω; R_0603_1608Metric; LCSC C22775
R54, R55, R56: 10kΩ; R_0603_1608Metric; LCSC C2906982
R57: 10kΩ; R_0603_1608Metric; LCSC C21190

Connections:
+3V3: C63.2, R55.1, R57.1; also elsewhere on the board
/TAPE_IN: Q4.3 (C), R57.2; also elsewhere on the board
/Tape/TAPE: C62.1, J8.T, R53.1
GND: C63.1, J8.S, Q3.2 (E), Q4.2 (E), R53.2; also elsewhere on the board
unnamed: C62.2, R54.1
unnamed: D4.2 (A), Q3.3 (C), R55.2, R56.1
unnamed: D4.1 (K), Q3.1 (B), R54.2
unnamed: Q4.1 (B), R56.2
